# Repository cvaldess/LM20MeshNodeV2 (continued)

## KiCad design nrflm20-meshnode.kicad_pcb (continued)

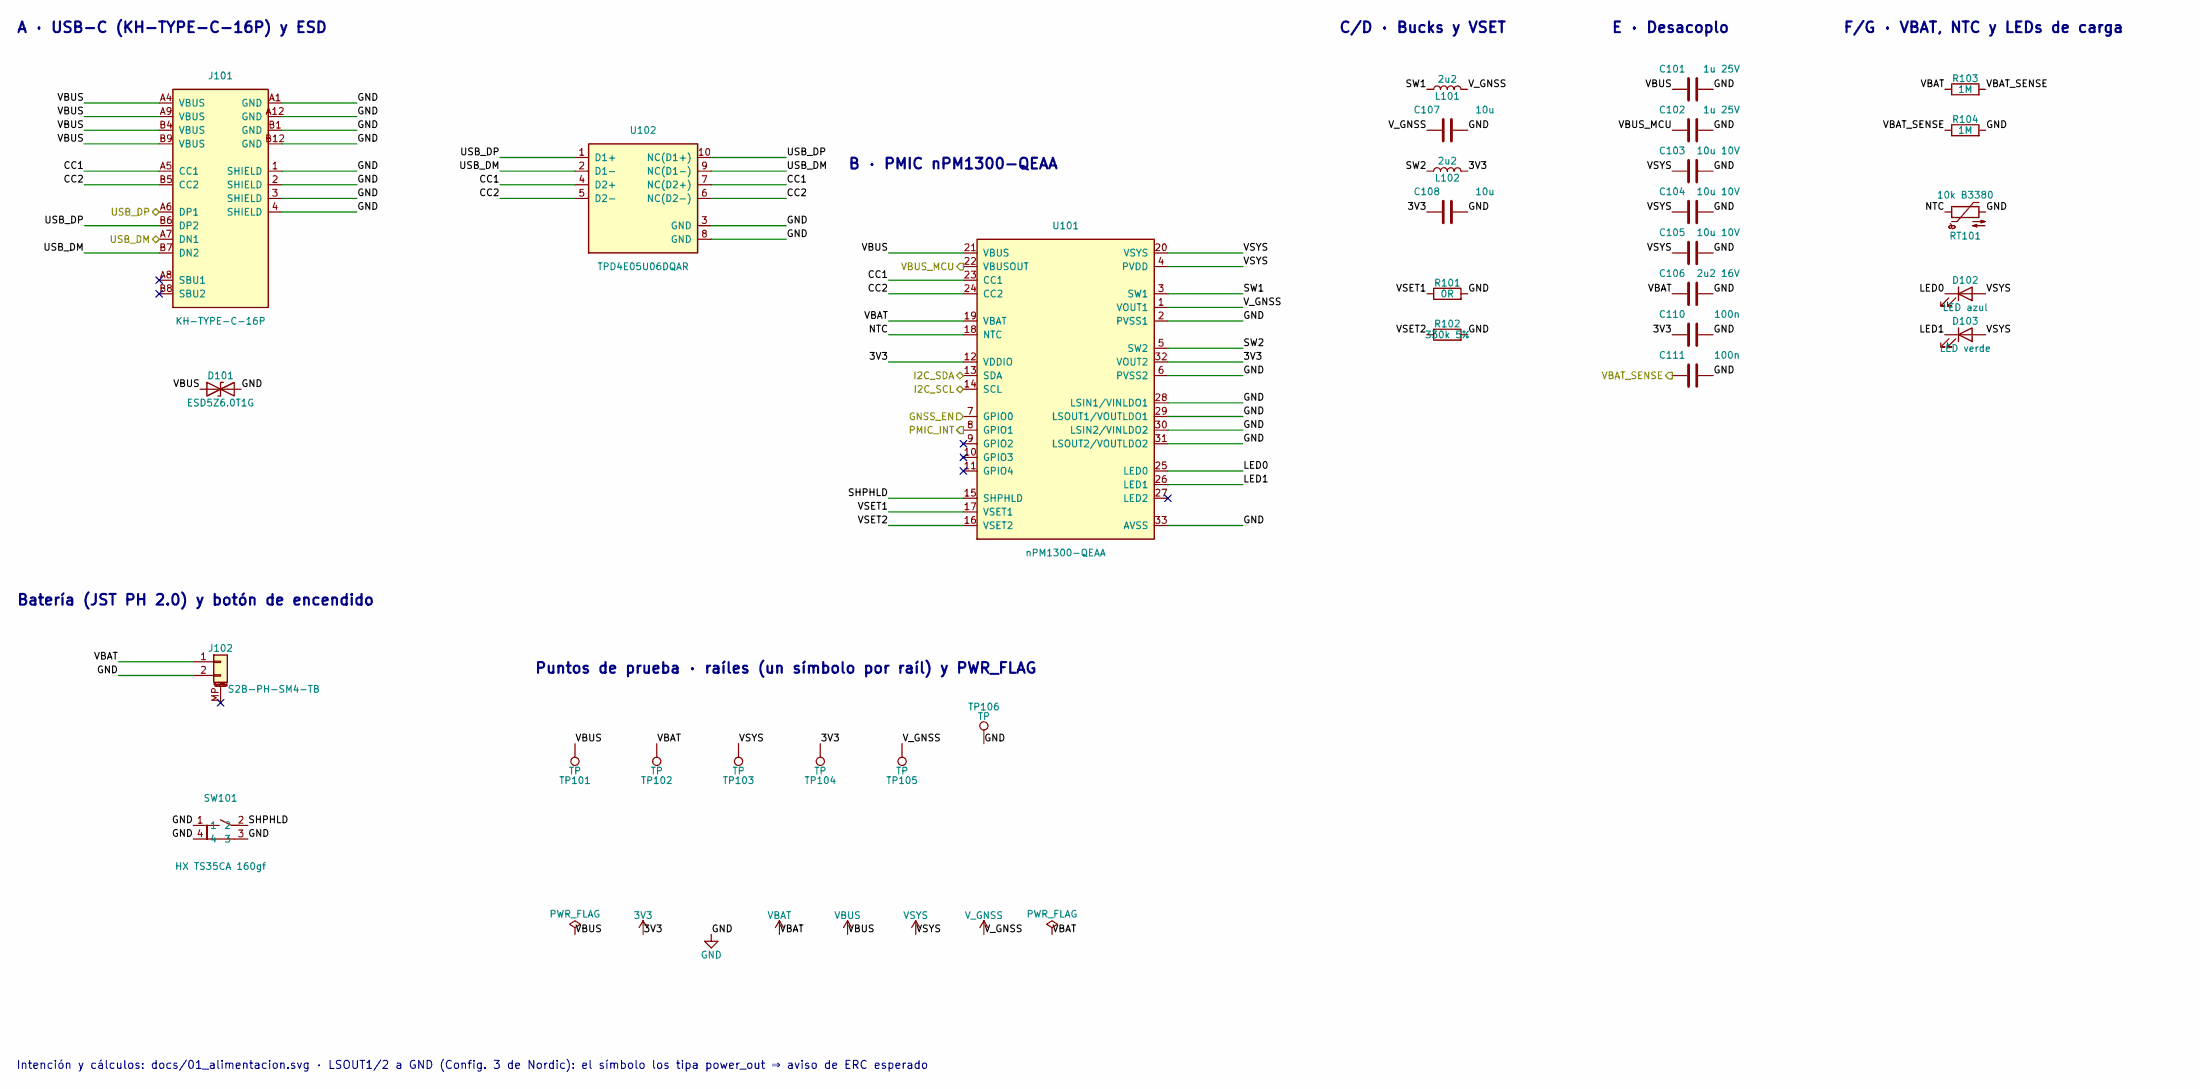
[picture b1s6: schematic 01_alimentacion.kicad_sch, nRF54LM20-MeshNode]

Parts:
C101, C102: 1u 25V; C_0402_1005Metric; MPN CL05A105KA5NQNC; LCSC Part C52923
C103, C104, C105: 10u 10V; C_0603_1608Metric
C106: 2u2 16V; C_0603_1608Metric; MPN CL10A225KO8NNNC; LCSC Part C23630
C107, C108: 10u; C_0603_1608Metric
C110, C111: 100n; C_0402_1005Metric; MPN CL05B104KO5NNNC; LCSC Part C1525
D101: ESD5Z6.0T1G; SOD-523F_L1.2-W0.8-LS1.7-RD; MPN ESD5Z6.0T1G; LCSC Part C82323
D102: LED azul; LED_0603_1608Metric; MPN XL-1608UBC-06A; LCSC Part C7371904
D103: LED verde; LED_0603_1608Metric; MPN XL-1608UGC-06A; LCSC Part C7371903
J101: KH-TYPE-C-16P; USB-C-SMD_KH-TYPE-C-16P; MPN KH-TYPE-C-16P; LCSC Part C709357
J102: S2B-PH-SM4-TB; JST_PH_S2B-PH-SM4-TB_1x02-1MP_P2.00mm_Horizontal; MPN S2B-PH-SM4-TB(LF)(SN); LCSC Part C295747
L101, L102: 2u2; L_Changjiang_FTC201610S; MPN APH201610C2R2MP01; LCSC Part C42455301
R101: 0R; R_0402_1005Metric; MPN RC0402FR-070RL; LCSC Part C106231
R102: 330k 5%; R_0402_1005Metric; MPN RC0402JR-07330KL; LCSC Part C137882
R103, R104: 1M; R_0402_1005Metric; MPN RC0402FR-071ML; LCSC Part C138033
RT101: 10k B3380; R_0402_1005Metric; MPN NCP15XH103F0SRC; LCSC Part C91636
SW101: HX TS35CA 160gf; KEY-SMD_HX-TS35CA-250GF; MPN HX TS35CA 160gf; LCSC Part C25168837
TP101, TP102, TP103, TP104, TP105, TP106: TP; TestPoint_Pad_D1.0mm
U101: nPM1300-QEAA; nPM1300-QFN32-EP3.5; MPN nPM1300-QEAA; LCSC Part C7501206
U102: TPD4E05U06DQAR; DFN2510-10_L2.5-W1.0-P0.50-BL; MPN TPD4E05U06DQAR; LCSC Part C22390021

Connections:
3V3: C108.1, C110.1, L102.2, TP104.1 (1_1), U101.12 (VDDIO), U101.32 (VOUT2); also elsewhere on the board
/01_alimentacion/CC1: J101.A5 (CC1), U101.23 (CC1), U102.4 (D2+), U102.7 (NC(D2+))
/01_alimentacion/CC2: J101.B5 (CC2), U101.24 (CC2), U102.5 (D2-), U102.6 (NC(D2-))
/01_alimentacion/LED0: D102.1 (K), U101.25 (LED0)
/01_alimentacion/LED1: D103.1 (K), U101.26 (LED1)
/01_alimentacion/NTC: RT101.1, U101.18 (NTC)
/01_alimentacion/SHPHLD: SW101.2, U101.15 (SHPHLD)
/01_alimentacion/SW1: L101.1, U101.3 (SW1)
/01_alimentacion/SW2: L102.1, U101.5 (SW2)
/01_alimentacion/VSET1: R101.1, U101.17 (VSET1)
/01_alimentacion/VSET2: R102.1, U101.16 (VSET2)
/GNSS_EN: U101.7 (GPIO0); also elsewhere on the board
/I2C_SCL: U101.14 (SCL); also elsewhere on the board
/I2C_SDA: U101.13 (SDA); also elsewhere on the board
/PMIC_INT: U101.8 (GPIO1); also elsewhere on the board
/USB_DM: J101.A7 (DN1), J101.B7 (DN2), U102.2 (D1-), U102.9 (NC(D1-)); also elsewhere on the board
/USB_DP: J101.A6 (DP1), J101.B6 (DP2), U102.1 (D1+), U102.10 (NC(D1+)); also elsewhere on the board
/VBAT_SENSE: C111.1, R103.2, R104.1; also elsewhere on the board
/VBUS_MCU: C102.1, U101.22 (VBUSOUT); also elsewhere on the board
GND: C101.2, C102.2, C103.2, C104.2, C105.2, C106.2, C107.2, C108.2, C110.2, C111.2, D101.2 (A2), J101.1 (SHIELD), J101.2 (SHIELD), J101.3 (SHIELD), J101.4 (SHIELD), J101.A1 (GND), J101.A12 (GND), J101.B1 (GND), J101.B12 (GND), J102.2, R101.2, R102.2, R104.2, RT101.2, SW101.1, SW101.3, SW101.4, TP106.1 (1_1), U101.2 (PVSS1), U101.6 (PVSS2), U101.28 (LSIN1/VINLDO1), U101.29 (LSOUT1/VOUTLDO1), U101.30 (LSIN2/VINLDO2), U101.31 (LSOUT2/VOUTLDO2), U101.33 (AVSS), U102.3 (GND), U102.8 (GND); also elsewhere on the board
VBAT: C106.1, J102.1, R103.1, TP102.1 (1_1), U101.19 (VBAT)
VBUS: C101.1, D101.1 (A1), J101.A4 (VBUS), J101.A9 (VBUS), J101.B4 (VBUS), J101.B9 (VBUS), TP101.1 (1_1), U101.21 (VBUS)
VSYS: C103.1, C104.1, C105.1, D102.2 (A), D103.2 (A), TP103.1 (1_1), U101.4 (PVDD), U101.20 (VSYS); also elsewhere on the board
V_GNSS: C107.1, L101.2, TP105.1 (1_1), U101.1 (VOUT1); also elsewhere on the board

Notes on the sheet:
B · PMIC nPM1300-QEAA
E · Desacoplo
F/G · VBAT, NTC y LEDs de carga
C/D · Bucks y VSET
Puntos de prueba · raíles (un símbolo por raíl) y PWR_FLAG
Batería (JST PH 2.0) y botón de encendido
A · USB-C (KH-TYPE-C-16P) y ESD
Intención y cálculos: docs/01_alimentacion.svg · LSOUT1/2 a GND (Config. 3 de Nordic): el símbolo los tipa power_out ⇒ aviso de ERC esperado

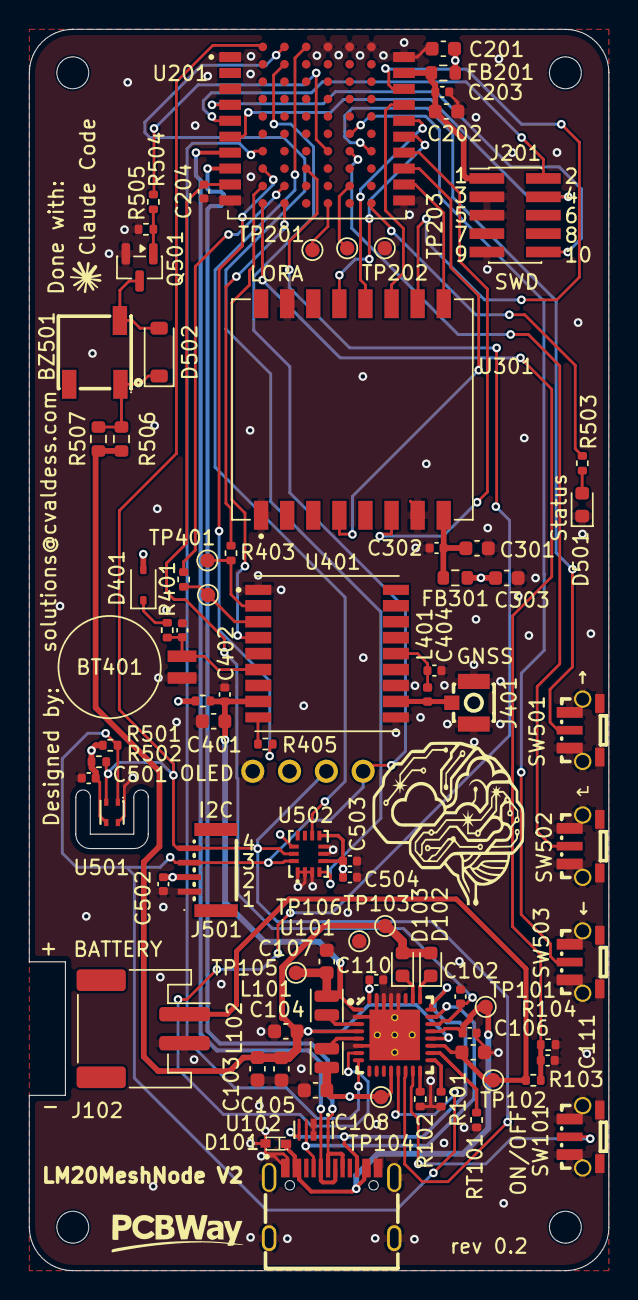
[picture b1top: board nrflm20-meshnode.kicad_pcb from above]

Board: 4 copper layers, 40.0 x 85.7 mm, 88 parts (1 on the bottom side), 60 nets.

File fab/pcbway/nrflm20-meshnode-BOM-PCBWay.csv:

"Designator","Qty","Manufacturer","Mfg Part #","Description/Value","Package/Footprint","LCSC Part #"
"BZ501","1","Huayu","HYG-5020A","HYG-5020A","easyeda2kicad:BUZ-SMD_3P-L5.0-W5.0-P3.50-BL","C7544810"
"C101,C102,C204,C502","4","Samsung","CL05A105KA5NQNC","1u 25V","Capacitor_SMD:C_0402_1005Metric","C52923"
"C103,C104,C105,C107,C108,C201,C202,C303,C401","9","Generic","","10uF 20% 10V X7R 0603","Capacitor_SMD:C_0603_1608Metric",""
"C106","1","Samsung","CL10A225KO8NNNC","2u2 16V","Capacitor_SMD:C_0603_1608Metric","C23630"
"C110,C111,C203,C302,C402,C403,C501,C503,C504","9","Samsung","CL05B104KO5NNNC","100n","Capacitor_SMD:C_0402_1005Metric","C1525"
"C301","1","Generic","","22uF 20% 10V X7R 0603","Capacitor_SMD:C_0603_1608Metric",""
"C404","1","FH","0402CG470F500NT","47p C0G","Capacitor_SMD:C_0402_1005Metric","C42563629"
"D101","1","onsemi","ESD5Z6.0T1G","ESD5Z6.0T1G","easyeda2kicad:SOD-523F_L1.2-W0.8-LS1.7-RD","C82323"
"D102","1","XINGLIGHT","XL-1608UBC-06A","Blue LED","LED_SMD:LED_0603_1608Metric","C7371904"
"D103,D501","2","XINGLIGHT","XL-1608UGC-06A","Green LED","LED_SMD:LED_0603_1608Metric","C7371903"
"D401","1","Diodes Incorporated","BAT54WS-7-F","BAT54WS","Diode_SMD:D_SOD-323","C124205"
"D502","1","JSMSEMI","1N4148W","1N4148W","Diode_SMD:D_SOD-123","C917030"
"DS501","1","HS","HS91L02W2C01","HS91L02W2C01","easyeda2kicad:OLED-TH_L38.0-W12.0_HS91L02W2C01","C5248081"
"FB201,FB301","2","Generic","","0R 0603 jumper","Resistor_SMD:R_0603_1608Metric",""
"J101","1","Kinghelm","KH-TYPE-C-16P","KH-TYPE-C-16P","easyeda2kicad:USB-C-SMD_KH-TYPE-C-16P","C709357"
"J102","1","JST","S2B-PH-SM4-TB(LF)(SN)","S2B-PH-SM4-TB","Connector_JST:JST_PH_S2B-PH-SM4-TB_1x02-1MP_P2.00mm_Horizontal","C295747"
"J201","1","HANXIA","HX PZ1.27-2x5P TP","SWD 2x5 1.27","Connector_PinHeader_1.27mm:PinHeader_2x05_P1.27mm_Vertical_SMD","C41376037"
"J401","1","BAT WIRELESS","BWU.FL-IPEX1","U.FL GNSS","easyeda2kicad:IPEX-SMD_BWIPX-1-001E","C5137195"
"J501","1","BOOMELE","1.0T-4P","Qwiic 1.0T-4P","meshnode:BOOMELE_1.0T-4P_1x04-1MP_P1.00mm_Horizontal","C970137"
"L101,L102","2","APV","APH201610C2R2MP01","2u2","Inductor_SMD:L_Changjiang_FTC201610S","C42455301"
"L401","1","Murata","LQW15AN47NJ00D","47nH (active GNSS antenna bias)","Inductor_SMD:L_0402_1005Metric","C192855"
"Q501","1","HT (Jin Yu)","BSS138","BSS138","Package_TO_SOT_SMD:SOT-23","C27140738"
"R101","1","Yageo","RC0402FR-070RL","0R","Resistor_SMD:R_0402_1005Metric","C106231"
"R102","1","Yageo","RC0402JR-07330KL","330k 5%","Resistor_SMD:R_0402_1005Metric","C137882"
"R103,R104","2","Yageo","RC0402FR-071ML","1M","Resistor_SMD:R_0402_1005Metric","C138033"
"R401,R402,R403","3","UNI-ROYAL","0402WGF1001TCE","1k","Resistor_SMD:R_0402_1005Metric","C11702"
"R501,R502","2","Yageo","RC0402FR-074K7L","4k7","Resistor_SMD:R_0402_1005Metric","C105871"
"R503","1","UNI-ROYAL","0402WGF4700TCE","470R","Resistor_SMD:R_0402_1005Metric","C25117"
"R504","1","UNI-ROYAL","0402WGF2200TCE","220R","Resistor_SMD:R_0402_1005Metric","C25091"
"R505","1","Yageo","RC0402FR-07100KL","100k","Resistor_SMD:R_0402_1005Metric","C60491"
"R506,R507","2","Generic","","10R 5% 0603","Resistor_SMD:R_0603_1608Metric",""
"RT101","1","Murata","NCP15XH103F0SRC","10k B3380","Resistor_SMD:R_0402_1005Metric","C91636"
"SW101,SW501,SW502,SW503","4","Hanxia","HX TS35CA 160gf","HX TS35CA 160gf","easyeda2kicad:KEY-SMD_HX-TS35CA-250GF","C25168837"
"U101","1","Nordic Semiconductor","nPM1300-QEAA","nPM1300-QEAA","meshnode:nPM1300-QFN32-EP3.5","C7501206"
"U102","1","DOWO","TPD4E05U06DQAR","TPD4E05U06DQAR","easyeda2kicad:DFN2510-10_L2.5-W1.0-P0.50-BL","C22390021"
"U201","1","Minew","ME54BS13 (nRF54LM20A)","ME54BS13","meshnode:ME54BS13",""
"U301","1","MinewSemi","MS21SF1-SX1262","MS21SF1-SX1262","meshnode:MS21SF1",""
"U401","1","MinewSemi","ME31GR02","ME31GR02","meshnode:ME31GR02",""
"U501","1","Nyfea","SHT41-P-NF","SHT41-P-NF","easyeda2kicad:DFN-4_L1.5-W1.5-SHT41-AD1B-R2","C55108905"
"U502","1","STMicroelectronics","LSM6DS3TR-C","LSM6DS3TR-C","easyeda2kicad:LGA-14_L3.0-W2.5-P0.50-TL","C967633"

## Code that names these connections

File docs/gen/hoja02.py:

"""Hoja 02 · MCU — ME54BS13 (nRF54LM20A), desacoplo, SWD, UART de depuración (docs/02_mcu.svg). Referencias 2xx.
Fuentes: Minew ME54BS13 datasheet v1.0.0 (pinout p.6-9, §7 PCB), nRF54LM20A datasheet v1.0 (clock pins p.1240,
SERIALxx por puerto, GPIOTE por puerto). El mapa de pines MAPA es la fuente para la captura y para la variante."""
import os

from svgkit import *  # noqa: F401,F403
from me54bs13_pads import pinmap as PADS  # pad -> nombre de puerto

OUT = os.path.normpath(os.path.join(os.path.dirname(os.path.abspath(__file__)), "..", "02_mcu.svg"))

# señal -> (puerto, tipo de etiqueta, periférico / nota)
MAPA = {
    "LORA_SCK": ("P1.17", "sig", "SPIM22 SCK (clock pin) · castellado 16"),
    "LORA_MOSI": ("P1.16", "sig", "SPIM22 MOSI · castellado 17"),
    "LORA_MISO": ("P1.15", "sig", "SPIM22 MISO · castellado 18"),
    "LORA_NSS": ("P1.18", "sig", "GPIO · castellado 15"),
    "LORA_BUSY": ("P1.19", "sig", "GPIO entrada · castellado 14"),
    "LORA_DIO1": ("P1.23", "sig", "GPIOTE20 (IRQ) · castellado 13"),
    "LORA_NRST": ("P1.26", "sig", "GPIO · castellado 12"),
    "I2C_SDA": ("P0.03", "sig", "TWIM30 SDA (como la DK)"),
    "I2C_SCL": ("P0.04", "sig", "TWIM30 SCL (clock pin)"),
    "IMU_INT1": ("P0.02", "sig", "GPIOTE30 ← INT1 del LSM6DS3TR-C"),
    "IMU_INT2": ("P0.05", "sig", "GPIOTE30 ← INT2 del LSM6DS3TR-C"),
    "GNSS_TX": ("P1.03", "sig", "UARTE20 TXD → RXD del GNSS"),
    "GNSS_RX": ("P1.29", "sig", "UARTE20 RXD ← TXD del GNSS"),
    "GNSS_PPS": ("P1.04", "sig", "GPIOTE20 (PIN_GPS_PPS)"),
    "GNSS_RST": ("P1.00", "sig", "sólo por R405 0 Ω DNP (RESET del GNSS al aire)"),
    "GNSS_EN": ("P1.05", "sig", "→ GPIO0 del nPM1300 (PIN_GPS_EN)"),
    "PMIC_INT": ("P1.06", "sig", "GPIOTE20 ← GPIO1 del nPM1300"),
    "VBAT_SENSE": ("P1.30", "sig", "AIN2 (BATTERY_PIN)"),
    "BTN_UP": ("P1.27", "sig", "GPIOTE20, pull-up interno"),
    "BTN_OK": ("P1.28", "sig", "GPIOTE20, pull-up interno (BUTTON1)"),
    "BTN_DOWN": ("P1.25", "sig", "GPIOTE20, pull-up interno"),
    "BUZZER": ("P1.09", "sig", "PWM20 (PIN_BUZZER)"),
    "LED_STAT": ("P2.00", "sig", "GPIO salida (PIN_LED1)"),
    "DBG_TX": ("P2.02", "loc", "UARTE00 TXD (pin dedicado) → TP201"),
    "DBG_RX": ("P2.07", "loc", "UARTE00 RXD (pin dedicado) ← TP202"),
}
PORT2PAD = {v: k for k, v in PADS.items() if v.startswith("P")}
NET_OF_PORT = {p: (n, k) for n, (p, k, _) in MAPA.items()}


def dibujar():
    W, H = 1720, 1340
    nueva(W, H, "02 · MCU — ME54BS13 (nRF54LM20A)",
          "nrf54lm20-meshnode rev 0.2 · hoja 2 · referencias 2xx · intención de 02_mcu.kicad_sch · mapa de pines mío")
    leyenda(760, 40)

    # ---------------------------------------------------------------- A · módulo
    frame(20, 76, 800, 1250, "A · U201 ME54BS13 — nRF54LM20A, antena PCB, cristales y DCDC internos")
    from simbolos_lib import me54bs13  # misma disposición que el símbolo de libs/meshnode.kicad_sym
    pins = me54bs13()
    left = sorted([p for p in pins if p["angle"] == 0], key=lambda p: -p["y"])
    right = sorted([p for p in pins if p["angle"] == 180], key=lambda p: -p["y"])
    top = max(p["y"] for p in pins if p["angle"] in (0, 180))

    def rows(side):
        out, prev = [], None
        for p in side:
            if prev is not None:
                out += [None] * (round((prev - p["y"]) / 2.54) - 1)
            out.append((p["number"], p["name"])); prev = p["y"]
        return out
    lr, rr = rows(left), rows(right)
    lr = [None] * round((top - left[0]["y"]) / 2.54) + lr
    e, h = ic2(300, 140, 250, "U201", "ME54BS13 · Minew", lr, rr, pitch=18.5, stub=22)
    spec = {}
    for p in pins:
        num, nm = p["number"], p["name"]
        port = nm.split("/")[0]
        if p["angle"] == 90:
            continue
        if port in NET_OF_PORT:
            spec[num] = NET_OF_PORT[port]
        elif nm.startswith("P"):
            spec[num] = ("", "nc")
    spec.update({"19": ("VCC_MCU", "loc"), "9": ("VBUS_MCU", "sig"), "8": ("USB_DP", "sig"), "7": ("USB_DM", "sig"),
                 "4": ("SWD_RST", "loc"), "5": ("SWDIO", "loc"), "6": ("SWDCLK", "loc"), "2": ("", "nc")})
    pin_labels(e, spec)
    gy = 140 + h + 10
    gnds = [p["number"] for p in pins if p["angle"] == 90]
    T(425, gy + 8, "GND: " + " · ".join(gnds) + "  (todas, con vía cada una)", "td", "middle")
    gnd(425, gy + 16)
    notes(40, gy + 56, [
        "Castellado 2 (RF) sin conectar: antena PCB del módulo (configuración por defecto).",
        "P1.01/P1.02 = NFC por defecto · P1.20/P1.21 = cristal de 32 kHz interno (no salen).",
        "Los GPIO libres quedan sin conectar (NC): el pad del módulo se suelda igual."])

    # ---------------------------------------------------------------- B · alimentación del módulo
    frame(840, 76, 860, 250, "B · Alimentación del módulo (Minew §7.3: π reservada junto a VCC)")
    label(890, 140, "3V3", "pwr", "end"); P([(890, 140), (980, 140)], "pw"); dot(940, 140)
    cap_v(940, 140, "C201", "10 µF", 44, "l"); gnd(940, 184)
    res_h(980, 140, "FB201", "0 Ω (o ferrita 600 Ω)", 90, sym="symp")
    P([(1070, 140), (1220, 140)], "pw"); dot(1110, 140); dot(1170, 140)
    cap_v(1110, 140, "C202", "10 µF", 44); gnd(1110, 184)
    cap_v(1170, 140, "C203", "100 nF", 44); gnd(1170, 184)
    label(1220, 140, "VCC_MCU", "loc")
    notes(860, 240, ["FB201 = π de Minew: 0 Ω de serie; ferrita (CBW160808U601T, cajón) si el",
                     "buck mete ruido en el BLE. C202/C203 a ≤ 0,5 mm de la pata 19, 2 vías a GND."])
    caps_to_gnd(1430, 140, "VBUS_MCU", "sig", [("C204", "1 µF 25 V")])
    notes(1350, 240, ["VBUS del módulo (pata 9): alimenta", "el regulador del PHY USB interno."])

    # ---------------------------------------------------------------- C · SWD
    frame(840, 340, 430, 270, "C · SWD — cabecera Cortex 2×5 1,27 mm")
    ej, _ = ic2(990, 400, 100, "J201", "2×5 1,27 SMD", [("1", "VTref"), ("3", "GND"), ("5", "GND"), ("7", "KEY"), ("9", "GNDdet")],
                [("2", "SWDIO"), ("4", "SWCLK"), ("6", "SWO"), ("8", "NC"), ("10", "nRESET")], pitch=24, stub=20)
    pin_labels(ej, {"1": ("VCC_MCU", "loc"), "3": ("", "gnd"), "5": ("", "gnd"), "7": ("", "nc"), "9": ("", "gnd"),
                    "2": ("SWDIO", "loc"), "4": ("SWDCLK", "loc"), "6": ("", "nc"), "8": ("", "nc"),
                    "10": ("SWD_RST", "loc")})
    notes(856, 560, ["Sólo para grabar el bootloader la primera vez (luego UF2/DFU por USB).",
                     "SWO sin conectar: P2.07 se usa como RXD de depuración."])

    # ---------------------------------------------------------------- D · UART de depuración
    frame(1290, 340, 410, 270, "D · UART de depuración (UARTE00)")
    tp(1340, 410, "TP201"); label(1390, 410, "DBG_TX", "loc")
    tp(1340, 450, "TP202"); label(1390, 450, "DBG_RX", "loc")
    tp(1340, 490, "TP203"); label(1390, 490, "GND", "pwr")
    notes(1306, 536, ["Pines dedicados de UARTE00: TXD P2.02 y RXD P2.07.",
                      "Por si el USB nativo no arranca (consola del core).",
                      "Huella TestPoint:TestPoint_Pad_D1.0mm (todos los TP)."], dy=19)

    # ---------------------------------------------------------------- E · mapa de pines
    frame(840, 624, 860, 702, "E · Mapa de pines (base de la variante de Meshtastic)")
    rows_ = []
    for sig, (port, kind, note) in MAPA.items():
        pad = PORT2PAD[port]
        rows_.append((sig, port, pad, note))
    tabla(840, 664, 860, [860, 990, 1060, 1110], ["Señal", "Puerto", "Pad", "Periférico / nota"], rows_, dy=20,
          mono=(0, 1, 2))
    notes(856, 1262, [
        "Reglas del nRF54LM20A: SERIAL2x sólo en P1/P3, SERIAL30 en P0, SERIAL00 en P2; IRQ y SENSE sólo en P0/P1/P3;",
        "SCK/SCL en clock pins. LoRa: SPIM22 (como la DK) · GNSS: UARTE20 · I²C: TWIM30 · depuración: UARTE00.",
        ("MS21SF1: cristal pasivo y conmutador por DIO2 ⇒ variante sin SX126X_DIO3_TCXO_VOLTAGE ni RXEN/TXEN (P1.12/P1.13 libres).", "tw")], dy=18)
    guardar(OUT)


if __name__ == "__main__":
    dibujar()

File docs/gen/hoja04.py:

"""Hoja 04 · GNSS — MinewSemi ME31GR02 (rev 0.2) y U.FL para antena activa o pasiva (docs/04_gnss.svg). Refs 4xx.
Fuentes: ME31GR02 datasheet V1.0.0 (§2.9 modos, §3.2 V_BCKP 2,5-3,6 V, §3.3 consumo, §4.1 pinout LCC-18, §5.1
referencia: L 47 nH desde VCC_RF, 47 pF y pila BAT tras diodo + 100 Ω, §5.2-5.5 layout/alimentación/antena/UART,
§5.6 arranque) y respuestas de Minew (19-11: V_BCKP 12 µA, chip Beken BK166X; 20-11: RESET con pull-up interno).
Pila de respaldo: Seiko MS621FE FL11E, especificación STDE-B-MS0621E-5ATFL11E (§4 carga 2,8-3,3 V, 3,1 recomendada,
máx. 0,5 mA a 3,1 V y 10 mA a 0 V; §8 sólo soldador, sin reflujo; plano E65 FL11E: + arriba en vista superior).
Pinout = simbolos_lib.me31gr02()."""
import os

from svgkit import *  # noqa: F401,F403

OUT = os.path.normpath(os.path.join(os.path.dirname(os.path.abspath(__file__)), "..", "04_gnss.svg"))


def dibujar():
    W, H = 1720, 1040
    nueva(W, H, "04 · GNSS — MinewSemi ME31GR02 (L1, 4 constelaciones)",
          "nrf54lm20-meshnode rev 0.2 · hoja 4 · referencias 4xx · intención de 04_gnss.kicad_sch")
    leyenda(760, 40)

    # ---------------------------------------------------------------- A · módulo
    frame(20, 76, 860, 610, "A · U401 ME31GR02 — Beken BK1661, LCC-18 10,5 × 9,7 (pinout tipo u-blox MAX)")
    L = [("8", "VCC"), ("6", "V_BCKP"), None, ("3", "RXD"), ("2", "TXD"), None, ("9", "RESET"), ("4", "PPS"), None,
         ("1", "GND"), ("10", "GND"), ("12", "GND")]
    R = [("11", "RF_IN"), ("14", "VCC_RF"), None] + [(n, "NC") for n in ("5", "7", "13", "15", "16", "17", "18")]
    e, h = ic2(360, 150, 180, "U401", "ME31GR02 · MinewSemi", L, R, pitch=26)
    pin_labels(e, {"8": ("V_GNSS", "pwr"), "6": ("V_BCKP", "loc"), "3": ("GNSS_RXD", "loc"),
                   "2": ("GNSS_TXD", "loc"), "9": ("GNSS_RESET", "loc"), "4": ("GNSS_PPS", "sig"),
                   "1": ("", "gnd"), "10": ("", "gnd"), "12": ("", "gnd"), "11": ("GNSS_RFIN", "loc"),
                   "14": ("VCC_RF", "loc"), **{n: ("", "nc") for n in ("5", "7", "13", "15", "16", "17", "18")}})
    notes(40, 150 + h + 36, [
        "UART 115200 por defecto, NMEA 4.1 (§5.5). Consumo (§3.3): 19 mA captura · 17,5 mA seguimiento.",
        "V_BCKP (2,5–3,6 V, 12 µA): pila BT401 cargada desde 3V3 (marco D) ⇒ RTC + efemérides vivos también",
        "con la placa apagada (ship mode o LiPo agotada) ⇒ arranque en caliente (~1 s) al volver a encender.",
        "RESET: pull-up interno (Minew 20-11) ⇒ al aire; R405 0 Ω DNP a GNSS_RST (P1.00) por si hiciera falta.",
        "PPS a 3,3 V directo a GNSS_PPS (P1.04). NC 5, 7, 13, 15–18 al aire (§4.1). Sin SAFEBOOT: actualiza por UART.",
        ("Meshtastic no lo reconoce: hace falta sonda nueva en GPS.cpp ($POLCFGPTVER → $POLRS; al arrancar", "tw"),
        ("saca $POLRS o $BKCHIP). Comandos $POLCFG… en datasheets/BK166X_Series_Interface_Description.", "tw"),
        "Frente a la rev 0.1 (E108-GN04S): fuera C404 56 pF en serie y TP401 SAFEBOOT; L401 82 → 47 nH; C404 = 47 pF",
        "de VCC_RF a GND; nuevos R405 (RESET), TP401/TP402 (UART) y pila de respaldo BT401 + D401."], dy=19)

    # ---------------------------------------------------------------- B · UART, reset, TP
    frame(900, 76, 800, 330, "B · UART, reset y puntos de prueba")
    label(990, 140, "GNSS_TX", "sig", "end"); res_h(990, 140, "R402", "1 kΩ", 80); label(1070, 140, "GNSS_RXD", "loc")
    label(990, 185, "GNSS_RX", "sig", "end"); res_h(990, 185, "R403", "1 kΩ", 80); label(1070, 185, "GNSS_TXD", "loc")
    label(990, 230, "GNSS_RST", "sig", "end"); res_h(990, 230, "R405", "0 Ω DNP", 80, sym="dnp")
    label(1070, 230, "GNSS_RESET", "loc")
    tp(1340, 140, "TP401"); label(1400, 140, "GNSS_TXD", "loc")
    tp(1340, 185, "TP402"); label(1400, 185, "GNSS_RXD", "loc")
    notes(920, 300, [
        "R402/R403 1 kΩ en serie (Minew pone 100 Ω): además limitan lo que entra por RXD con el GNSS apagado.",
        ("§2.9/§5.5: con VCC cortado ninguna línea en alto ⇒ FIRMWARE: al apagar, TX del MCU en entrada + pull-down.", "tw"),
        "R405 sin montar: RESET queda con su pull-up y el MCU no puede dejarlo en alto con el GNSS apagado.",
        "TP401/TP402: la UART del GNSS a mano para probar los $POLCFG… o actualizar su firmware (con el nRF en reset).",
        "Con BT401 el GNSS está en backup aunque la placa esté apagada: tampoco entonces se le mete nada por la UART."],
        dy=19)

    # ---------------------------------------------------------------- C · antena
    frame(900, 420, 800, 266, "C · Antena 1575 MHz por U.FL — activa o pasiva (Minew §5.1)")
    ej, _ = ic2(940, 500, 110, "J401", "BWU.FL-IPEX1", [], [("1", "SIG"), ("2", "GND"), ("3", "GND")], pitch=24)
    for k in ("2", "3"):
        x, y = ej[k]; P([(x, y), (x + 10, y)]); gnd(x + 10, y)
    x0, y0 = ej["1"]
    P([(x0, y0), (1300, y0)], "rf"); dot(1200, y0); label(1300, y0, "GNSS_RFIN", "loc")
    P([(1200, y0), (1200, y0 + 12)])
    ind_v(1200, y0 + 12, "L401", "47 nH (activa)", 60)
    yb = y0 + 72
    dot(1200, yb); P([(1200, yb), (1250, yb)]); cap_v(1250, yb, "C404", "47 pF C0G", 40); gnd(1250, yb + 40)
    P([(1180, yb), (1200, yb)]); label(1180, yb, "VCC_RF", "loc", "end")
    notes(1320, 556, ["L401 desde VCC_RF (3,3 V) alimenta una antena",
                      "activa por el coaxial; C404 desacopla VCC_RF.",
                      "Sin condensador serie: como la referencia,",
                      "la polarización entra por RF_IN.",
                      "Pasiva: L401 no estorba si la antena no",
                      "está en corto en DC. Activa: G < 25 dB, NF < 1,5."], dy=17)
    notes(920, 668, ["Pista 50 Ω coplanar de RF_IN al U.FL, corta, referida a In1 (GND) como en la rev 0.1 (§5.2)."])

    # ---------------------------------------------------------------- D · alimentación y respaldo
    frame(20, 700, 860, 330, "D · Alimentación del GNSS y pila de respaldo de V_BCKP")
    caps_to_gnd(120, 760, "V_GNSS", "pwr", [("C401", "10 µF"), ("C402", "100 nF")], dx=90)
    label(500, 760, "3V3", "pwr", "end"); res_h(500, 760, "R404", "0 Ω DNP", 80, sym="dnp"); label(580, 760, "V_GNSS", "pwr")
    yk = 850
    label(100, yk, "3V3", "pwr", "end"); diode_h(100, yk, "D401", "BAT54WS", 70); P([(170, yk), (190, yk)])
    res_h(190, yk, "R401", "1 kΩ", 80); P([(270, yk), (440, yk)]); dot(320, yk); dot(400, yk)
    bat_v(320, yk, "BT401", "MS621FE-FL11E", 48, side="l"); gnd(320, yk + 48)
    cap_v(400, yk, "C403", "100 nF", 40); gnd(400, yk + 40)
    label(440, yk, "V_BCKP", "loc")
    notes(520, 822, ["BT401: Li-Mn recargable 3 V, 5,5 mAh, Ø 6,8 × 2,1 mm.",
                     "Carga 2,8–3,3 V (3,1 recomendada): 3V3 − BAT54 ≈ 3,15 V;",
                     "R401 limita a ≤ 3 mA con la pila a 0 V (Seiko: máx. 10).",
                     "D401 impide que la pila alimente el 3V3 apagado (fuga",
                     "< 1 µA a 3 V). Sin BT401 funciona igual que la rev 0.1.",
                     "Autonomía estimada ≈ 1–2 semanas de RTC a 12 µA.",
                     ("Sin reflujo: soldar a mano al final (≤ 5 s, pila < 85 °C).", "tw")], dy=17)
    notes(40, 950, ["V_GNSS = BUCK1 del nPM1300 (200 mA, sólo para el GNSS), conmutado con PIN_GPS_EN (GNSS_EN): lejos de los",
                    "picos de TX del MS21SF1. Minew §5.3 pide fuente limpia > 100 mA. C401/C402 junto a la pata 8, C403 junto a la 6.",
                    "R404 sin montar: GNSS siempre encendido desde 3V3 si BUCK1 diera guerra (dormiría por comando).",
                    ("🚨 Con R404 montada, BUCK1 debe quedar APAGADO (dos fuentes unidas).", "tw")], dy=19)

    rows = [("U401", "GNSS L1 (4 constel.)", "MinewSemi ME31GR02", "LCC-18 10,5×9,7", "—", "patrocinio Minew"),
            ("J401", "conector antena", "BWU.FL-IPEX1", "SMD", "C5137195", "cajón #210"),
            ("L401", "47 nH (antena activa)", "Murata LQW15AN47NJ00D", "0402", "C192855", "cajón #207"),
            ("C404", "47 pF C0G", "FH 0402CG470F500NT", "0402", "C42563629", "cajón #208"),
            ("BT401", "pila recargable 3 V", "Seiko MS621FE-FL11E", "Ø6,8 tags", "—", "COMPRAR"),
            ("D401", "Schottky baja fuga", "Diodes BAT54WS-7-F", "SOD-323", "C124205", "COMPRAR"),
            ("R401-R403", "1 kΩ 1 %", "UNI-ROYAL 0402WGF1001TCE", "0402", "C11702", "cajón #31"),
            ("R404 R405", "0 Ω (DNP)", "—", "0402", "—", "—"),
            ("C401", "10 µF 10 V X7R", "—", "0603", "—", "cajón #147"),
            ("C402 C403", "100 nF 16 V X7R", "Samsung CL05B104KO5NNNC", "0402", "C1525", "cajón #22"),
            ("TP401 TP402", "punto de prueba", "TestPoint_Pad_D1.0mm", "Ø1 mm", "—", "—")]
    frame(900, 700, 800, 330, "Piezas de la hoja")
    tabla(900, 740, 800, [920, 1010, 1160, 1350, 1450, 1545], ["Ref.", "Qué es", "Pieza", "Encaps.", "LCSC", "Stock"],
          rows, dy=23, mono=(0, 4))
    notes(920, 1019, ["BT401: huella Battery:BatteryHolder_Seiko_MS621F (pad 1 = +, plano Seiko E65 FL11E)."])
    guardar(OUT)


if __name__ == "__main__":
    dibujar()
